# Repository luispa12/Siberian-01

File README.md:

test

## Project Specification

[Link to the Github repository](https://github.com/luispa12/Siberian-01)

This board is based on the RP2040 microcontroller from the Raspberry Foundation. 

It is a development board with the minimun requirements for the RP2040 IC to properly works, it complies with the USB 2.0 protocol, full use of all the GPIO pins, on board linear regulator for the 3.3V, 1 led status and another led connected to pin GPIO17.

It was designed with the purpose to learn how to design, assemble, document and manufacture (JLCPCB) printed circuit boarda (PCB's).   

### SoC Features

* Dual ARM Cortex-M0+ @ 133MHz
* 264kB on-chip SRAM in six independent banks
* Support for up to 16MB of off-chip Flash memory via dedicated QSPI bus
* DMA controller
* Fully-connected AHB crossbar
* Interpolator and integer divider peripherals
* On-chip programmable LDO to generate core voltage
* 2 on-chip PLLs to generate USB and core clocks
* 30 GPIO pins, 4 of which can be used as analog inputs
* Peripherals:
   * 2 UARTs
   * 2 SPI controllers
   * 2 I2C controllers
   * 16 PWM channels
   * USB 1.1 controller and PHY, with host and device support
   * 8 PIO state machines

For the complete description of the microcontroller, see the [RP2040 DATASHEET](https://datasheets.raspberrypi.com/rp2040/rp2040-datasheet.pdf).

### Power

* USB Type B

#### Debug Pinout Connection 

| Pin number | SoC      | Description |
|------------|----------|---------    |
| 1          | 25       | SWD         |
| 2          | --       | GND         |
| 3          | 24       | SWCLK       |

### Pin Layout

Pin Layou pending...

#### Left Side

| Pin number | SoC      | Description                                 |
|------------|----------|---------                                    | 
| 1          | 2        | GPIO0, SPI0 RX, UART0 TX, I2C0 SDA.         |
| 2          | 3        | GPIO1, SPI0 CSn, UART0 RX, I2C0 SCL.        |
| 3          | 4        | GPIO2, SPI0 SCK, UART0 CTS, I2C1 SDA.       |
| 4          | 5        | GPIO3, SPI0 TX, UART0 RTS, I2C1 SCL.        |
| 5          | 6        | GPIO4, SPI0 RX, UART1 TX, I2C0 SDA.         |
| 6          | 7        | GPIO5, SPI0 CSn, UART1 RX, I2C0 SCL.        |
| 7          | --       | GND.                                        |
| 8          | 8        | GPIO6, SPI0 SCK, UART1 CTS, I2C1 SDA.       |
| 9          | 9        | GPIO7, SPI0 TX, UART1 RTS, I2C1 SCL.        |
| 10         | 11       | GPIO8, SPI1 RX, UART1 TX, I2C0 SDA.         |
| 11         | 12       | GPIO9, SPI1 CSn, UART1 RX, I2C0 SCL.        |
| 12         | 13       | GPIO10, SPI1 SCK UART1 CTS I2C1 SDA.        |
| 13         | 14       | GPIO11, SPI1 TX UART1 RTS I2C1 SCL.         |
| 14         | --       | GND.                                        |
| 15         | 15       | GPIO12, SPI1 RX, UART0 TX, I2C0 SDA.        |
| 16         | 16       | GPIO13, SPI1 CSn, UART0 RX, I2C0 SCL.       |
| 17         | 17       | GPIO14, SPI1 SCK, UART0 CTS, I2C1 SDA.      |
| 18         | 18       | GPIO15, SPI1 TX, UART0 RTS, I2C1 SCL.       |
| 19         | 27       | GPIO16, SPI0 RX, UART0 TX, I2C0 SDA.        |
| 20         | --       | GND.                                        |

#### Right Side

| Pin number | SoC      | Description                                        |
|------------|----------|--------------                                      |
| 21         | 28       | GPIO17, SPI0 CSn, UART0 RX, I2C0 SCL.              |
| 22         | 29       | GPIO18, SPI0 SCK, UART0 CTS, I2C1 SDA.             |
| 23         | 30       | GPIO19, SPI0 TX, UART0 RTS, I2C1 SCL.              |
| 24         | 31       | GPIO20, SPI0 RX, UART1 TX, I2C0 SDA, CLOCK GPIN0.  |
| 25         | 32       | GPIO21, SPI0 CSn, UART1 RX, I2C0 SCL, CLOCK GPOUT0.|
| 26         | 34       | GPIO22, SPI0 SCK, UART1 CTS, I2C1 SDA,CLOCK GPIN1. |
| 27         | --       | GND.                                               |
| 28         | 35       | GPIO23, SPI0 TX, UART1 RTS, I2C1 SCL, CLOCK GPOUT1.|
| 29         | 36       | GPIO24, SPI1 RX, UART1 TX, I2C0 SDA,  CLOCK GPOUT2.|
| 30         | 36       | GPIO25, SPI1 CSn, UART1 RX, I2C0 SCL, CLOCK GPOUT3.|
| 31         | 38       | GPIO26\_ADC0, SPI1 SCK, UART1 CTS, I2C1 SDA.       |
| 32         | 39       | GPIO27\_ADC1, SPI1 TX, UART1 RTS, I2C1 SCL.        |
| 33         | 40       | GPIO28\_ADC2, SPI1 RX, UART0 TX, I2C0 SDA.         |
| 34         | --       | GND.                                               |
| 35         | 41       | GPIO29\_ADC3,SPI1 CSn, UART0 RX, I2C0 SCL.         |
| 36         | 26       | RUN                                                |
| 37         | --       | VBUS                                               |
| 38         | --       | +3V3                                               |
| 39         | --       | GND.                                               |
| 40         | --       | GND.                                               |

| Function       | SoC                                                        | 
|------------    |----------                                                  |
| SPIx.          | Connect one of the internal PL022 SPI peripherals to GPIO. | 
| UARTx.          | Connect one of the internal PL011 UART peripherals to GPIO.|
| I2Cx.          | Connect one of the internal DW I2C peripherals to GPIO.    | 
| CLOCK GPINx.   | General purpose clock inputs. Can be routed to a number of internal clock domains on RP2040, e.g. to provide a 1Hz clock for the RTC, or can be connected to an internal frequency counter.  | 
| CLOCK GPOUTx.| General purpose clock outputs. Can drive a number of internal clocks (including PLLoutputs) onto GPIOs, with optional integer divide.|

## Board Design

Top

Bottom

## Bill of Material

[Interactive BOM](docs/bom/bom.html)

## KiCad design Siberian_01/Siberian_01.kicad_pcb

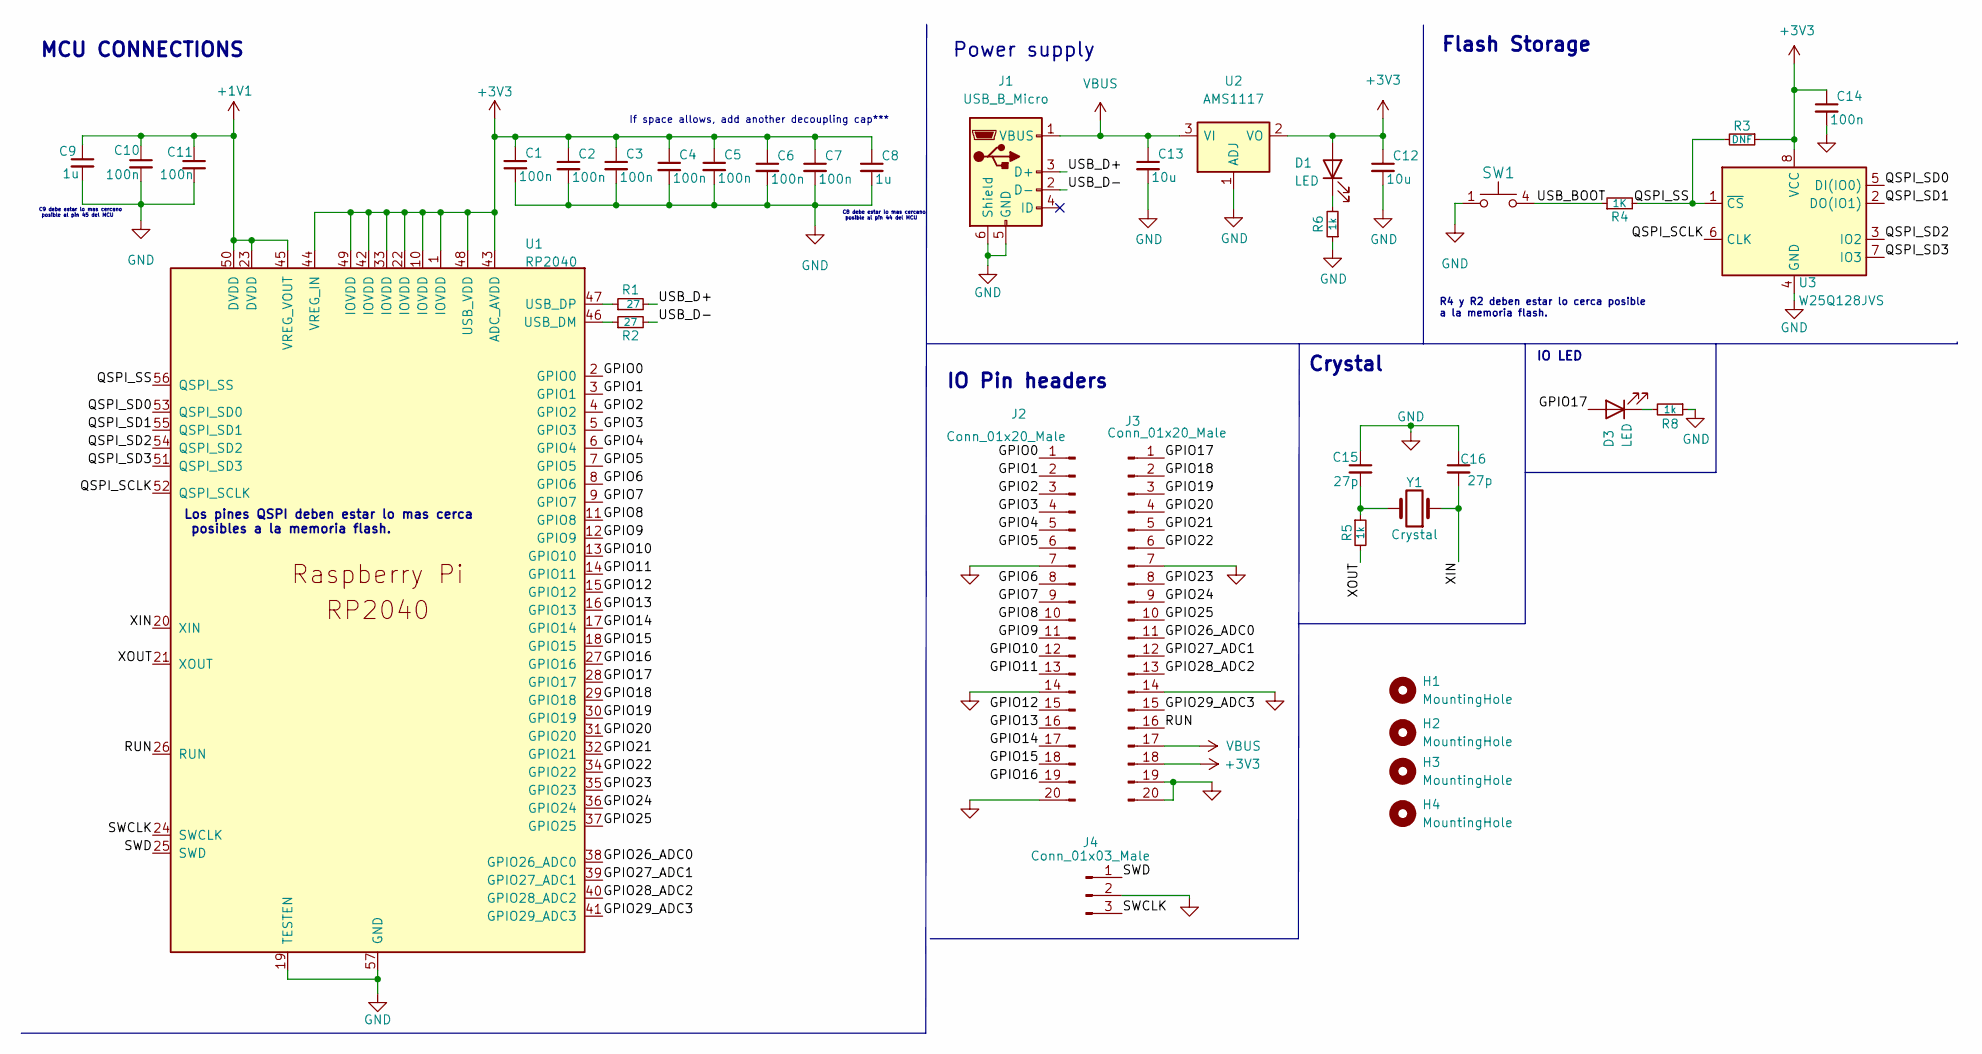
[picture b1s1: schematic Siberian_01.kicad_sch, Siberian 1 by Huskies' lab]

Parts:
C1, C2, C3, C4, C5, C6, C7, C10, C11, C14: 100n; C_0603_1608Metric
C8, C9: 1u; C_0603_1608Metric
C12, C13: 10u; C_0603_1608Metric
C15, C16: 27p; C_0603_1608Metric
D1, D3: LED; LED_0603_1608Metric
H1, H2, H3, H4: MountingHole; MountingHole_2.1mm
J1: USB_B_Micro; USB_Micro-B_Amphenol_10118194_Horizontal
J2, J3: Conn_01x20_Male; PinHeader_1x20_P2.54mm_Vertical
J4: Conn_01x03_Male; PinHeader_1x03_P2.54mm_Vertical
R1, R2: 27; R_0603_1608Metric
R3: DNF; R_0603_1608Metric
R4: 1K; R_0603_1608Metric
R5, R6, R8: 1k; R_0603_1608Metric
SW1: PTS815_SJM_250_SMTR_LFS; SW4_PTS815 SJM 250 SMTR LFS_CNK
U1: RP2040; RP2040-QFN-56
U2: AMS1117; SOT-223-3_TabPin2
U3: W25Q128JVS; SOIC-8_5.23x5.23mm_P1.27mm
Y1: Crystal; Crystal_SMD_HC49-US

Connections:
+1V1: C9.1, C10.1, C11.1, U1.23 (DVDD), U1.45 (VREG_VOUT), U1.50 (DVDD)
+3V3: C1.1, C2.1, C3.1, C4.1, C5.1, C6.1, C7.1, C8.1, C12.1, C14.1, D1.2 (A), J3.18, R3.1, U1.1 (IOVDD), U1.10 (IOVDD), U1.22 (IOVDD), U1.33 (IOVDD), U1.42 (IOVDD), U1.43 (ADC_AVDD), U1.44 (VREG_IN), U1.48 (USB_VDD), U1.49 (IOVDD), U2.2 (VO), U3.8 (VCC)
/GPIO0: J2.1, U1.2 (GPIO0)
/GPIO1: J2.2, U1.3 (GPIO1)
/GPIO2: J2.3, U1.4 (GPIO2)
/GPIO3: J2.4, U1.5 (GPIO3)
/GPIO4: J2.5, U1.6 (GPIO4)
/GPIO5: J2.6, U1.7 (GPIO5)
/GPIO6: J2.8, U1.8 (GPIO6)
/GPIO7: J2.9, U1.9 (GPIO7)
/GPIO8: J2.10, U1.11 (GPIO8)
/GPIO9: J2.11, U1.12 (GPIO9)
/GPIO10: J2.12, U1.13 (GPIO10)
/GPIO11: J2.13, U1.14 (GPIO11)
/GPIO12: J2.15, U1.15 (GPIO12)
/GPIO13: J2.16, U1.16 (GPIO13)
/GPIO14: J2.17, U1.17 (GPIO14)
/GPIO15: J2.18, U1.18 (GPIO15)
/GPIO16: J2.19, U1.27 (GPIO16)
/GPIO17: D3.2 (A), J3.1, U1.28 (GPIO17)
/GPIO18: J3.2, U1.29 (GPIO18)
/GPIO19: J3.3, U1.30 (GPIO19)
/GPIO20: J3.4, U1.31 (GPIO20)
/GPIO21: J3.5, U1.32 (GPIO21)
/GPIO22: J3.6, U1.34 (GPIO22)
/GPIO23: J3.8, U1.35 (GPIO23)
/GPIO24: J3.9, U1.36 (GPIO24)
/GPIO25: J3.10, U1.37 (GPIO25)
/GPIO26_ADC0: J3.11, U1.38 (GPIO26_ADC0)
/GPIO27_ADC1: J3.12, U1.39 (GPIO27_ADC1)
/GPIO28_ADC2: J3.13, U1.40 (GPIO28_ADC2)
/GPIO29_ADC3: J3.15, U1.41 (GPIO29_ADC3)
/QSPI_SCLK: U1.52 (QSPI_SCLK), U3.6 (CLK)
/QSPI_SD0: U1.53 (QSPI_SD0), U3.5 (DI(IO0))
/QSPI_SD1: U1.55 (QSPI_SD1), U3.2 (DO(IO1))
/QSPI_SD2: U1.54 (QSPI_SD2), U3.3 (IO2)
/QSPI_SD3: U1.51 (QSPI_SD3), U3.7 (IO3)
/QSPI_SS: R3.2, R4.2, U1.56 (QSPI_SS), U3.1 (~CS)
/RUN: J3.16, U1.26 (RUN)
/SWCLK: J4.3, U1.24 (SWCLK)
/SWD: J4.1, U1.25 (SWD)
/USB_BOOT: R4.1, SW1.4
/USB_D+: J1.3 (D+), R1.2
/USB_D-: J1.2 (D-), R2.2
/XIN: C16.2, U1.20 (XIN), Y1.1
/XOUT: R5.2, U1.21 (XOUT)
GND: C1.2, C2.2, C3.2, C4.2, C5.2, C6.2, C7.2, C8.2, C9.2, C10.2, C11.2, C12.2, C13.2, C14.2, C15.1, C16.1, J1.5 (GND), J1.6 (Shield), J2.7, J2.14, J2.20, J3.7, J3.14, J3.19, J3.20, J4.2, R6.1, R8.1, SW1.1, U1.19 (TESTEN), U1.57 (GND), U2.1 (ADJ), U3.4 (GND)
unnamed: C15.2, R5.1, Y1.2
unnamed: D1.1 (K), R6.2
unnamed: D3.1 (K), R8.2
unnamed: R1.1, U1.47 (USB_DP)
unnamed: R2.1, U1.46 (USB_DM)
VBUS: C13.1, J1.1 (VBUS), J3.17, U2.3 (VI)

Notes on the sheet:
Los pines QSPI deben estar lo mas cerca posibles a la memoria flash.
MCU CONNECTIONS
C8 debe estar lo mas cercano posible al pin 44 del MCU
R4 y R2 deben estar lo cerca posible a la memoria flash.
If space allows, add another decoupling cap***
Power supply
IO LED
C9 debe estar lo mas cercano posible al pin 45 del MCU
IO Pin headers
Flash Storage
Crystal

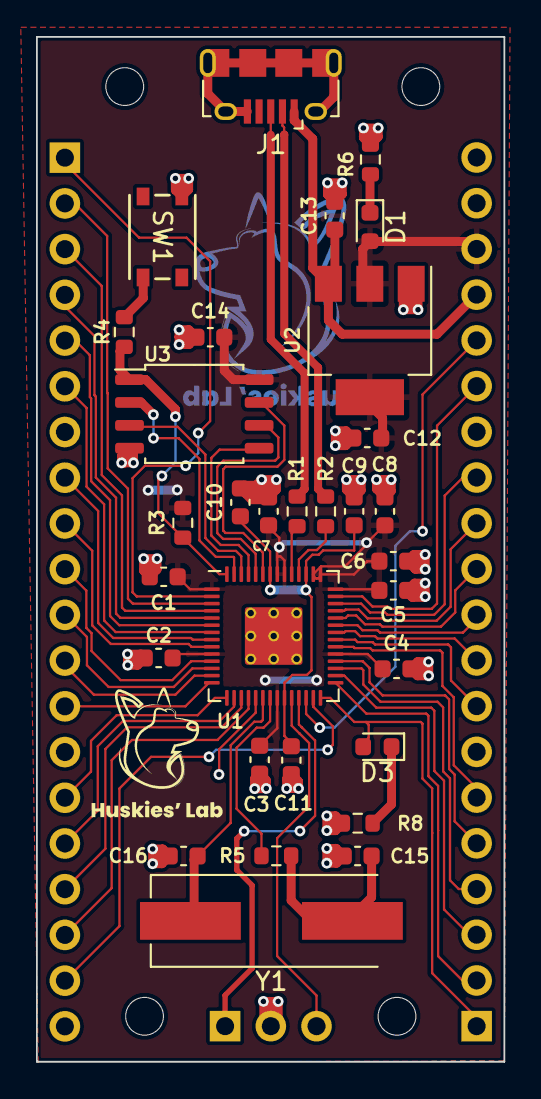
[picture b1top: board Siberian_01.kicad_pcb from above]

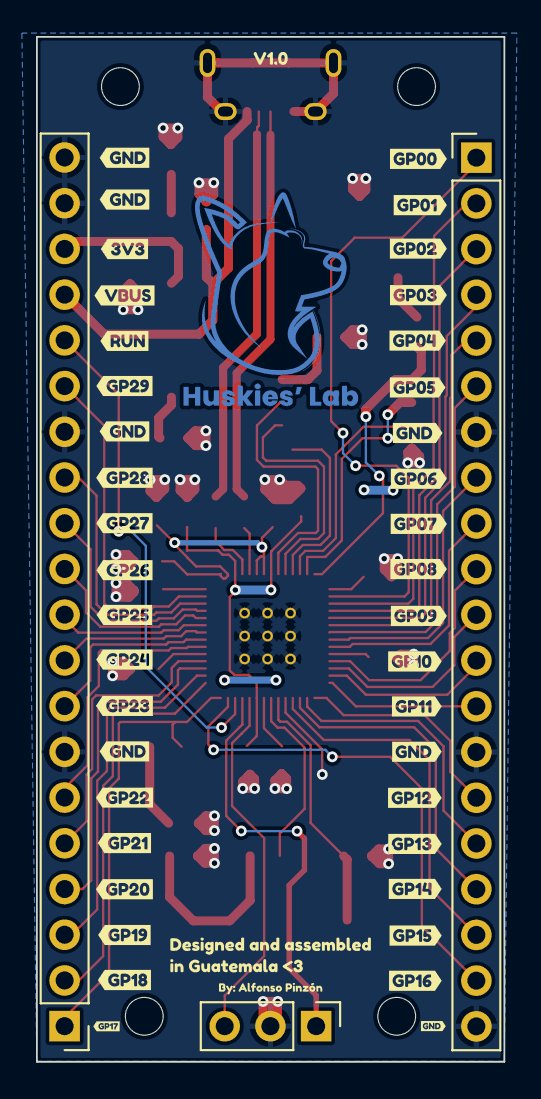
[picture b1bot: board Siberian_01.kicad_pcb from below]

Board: 2 copper layers, 26.0 x 56.9 mm, 81 parts (46 on the bottom side), 53 nets.

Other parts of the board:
kibuzzard-648F2C57: G***; kibuzzard-648F2C57
kibuzzard-648F2C96, kibuzzard-648F2C96#2, kibuzzard-648F2C96#3: G***; kibuzzard-648F2C96
kibuzzard-648F2CA2: G***; kibuzzard-648F2CA2
kibuzzard-648F2CB5: G***; kibuzzard-648F2CB5
kibuzzard-648F2CBD: G***; kibuzzard-648F2CBD
kibuzzard-648F2CC6: G***; kibuzzard-648F2CC6
kibuzzard-648F2CDB: G***; kibuzzard-648F2CDB
kibuzzard-648F2CE5: G***; kibuzzard-648F2CE5
kibuzzard-648F2D0C: G***; kibuzzard-648F2D0C
kibuzzard-648F2D2B: G***; kibuzzard-648F2D2B
kibuzzard-648F2D4D: G***; kibuzzard-648F2D4D
kibuzzard-648F2D5B: G***; kibuzzard-648F2D5B
kibuzzard-648F2D6A: G***; kibuzzard-648F2D6A
kibuzzard-648F2D18: G***; kibuzzard-648F2D18
kibuzzard-648F2D22: G***; kibuzzard-648F2D22
kibuzzard-648F2D43: G***; kibuzzard-648F2D43
kibuzzard-648F2D75: G***; kibuzzard-648F2D75
kibuzzard-648F36A4: G***; kibuzzard-648F36A4
kibuzzard-648F36AB: G***; kibuzzard-648F36AB
kibuzzard-648F36B6: G***; kibuzzard-648F36B6
kibuzzard-648F36C6: G***; kibuzzard-648F36C6
kibuzzard-648F38C2: G***; kibuzzard-648F38C2
kibuzzard-648F368A: G***; kibuzzard-648F368A
kibuzzard-648F369C: G***; kibuzzard-648F369C
kibuzzard-648F3652: G***; kibuzzard-648F3652
kibuzzard-648F3680: G***; kibuzzard-648F3680
kibuzzard-648F3832: G***; kibuzzard-648F3832
kibuzzard-648FA7D0: G***; kibuzzard-648FA7D0
kibuzzard-648FAA0F: G***; kibuzzard-648FAA0F
kibuzzard-649102A3: G***; kibuzzard-649102A3
kibuzzard-649102AA: G***; kibuzzard-649102AA
kibuzzard-649102B0: G***; kibuzzard-649102B0
kibuzzard-649102B6: G***; kibuzzard-649102B6
kibuzzard-649102CC: G***; kibuzzard-649102CC
kibuzzard-649102D1: G***; kibuzzard-649102D1
kibuzzard-649102D9: G***; kibuzzard-649102D9
kibuzzard-649102E1: G***; kibuzzard-649102E1
kibuzzard-649125AB: G***; kibuzzard-649125AB
kibuzzard-6491029F: G***; kibuzzard-6491029F
kibuzzard-64910299: G***; kibuzzard-64910299
kibuzzard-64910390: G***; kibuzzard-64910390

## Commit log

2023-06-29 Add files via upload
    photo for the read me file
2023-06-29 readme created
2023-06-29 ASSETS: added the photos for the bottom, top and and eschematic
2023-06-29 modification to files to have it more organized
2023-06-29 added the interactive bom and bom.cvs
2023-06-29 INTERACTRIVE BOOM
2023-06-29 added a readme file template from another spressif project
2023-06-29 README: added descriptio of the SOC
2023-06-29 readme: added the phoptos for the front and top view
2023-06-29 interactive bom
2023-06-29 Update README.md
    modifications
2023-06-29 Rename index.html to bom.html
    change the name of the file
2023-06-29 Update README.md
    modified the path
2023-06-29 Update README.md
    added the interactive boom
2023-06-29 added logo for the header
2023-06-30 added better description
2023-06-30 README: mopdified the path of the logo to actually works and and added the logo as a banner
2023-06-30 README: ADDED THE PATH
2023-06-30 added the interactie on the same repo and added the librarios for the switch
2023-06-30 README: added the link of the repo for github.
2023-06-30 readme: added description
2023-06-30 readme: vinetas
2023-07-03 README: added the pin description, and also a brief description of the project.
2023-07-03 README: modified the table since it was moved.
2023-10-21 Update README.md
    test 01
